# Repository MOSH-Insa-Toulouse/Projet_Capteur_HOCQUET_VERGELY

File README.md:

# Projet Banc de tests 

## Sommaire
<!-- TOC depthFrom:2 -->
  - [1. Description](#1-description)
  - [2. Installation](#2-installation)
  - [3. Code Arduino](#3-code-arduino)
  - [4. Shield KICAD](#4-shield)
  - [5. Application Android](#5-application-android)
  - [6. Etalonnage](#6-Etalonnage)
  - [7. Datasheet](#7-datasheet)
  - [8. Les auteurs](#8-les-auteurs)
<!-- /TOC -->

## 1. Description
Ce répertoire contient toutes les ressources nécessaires au  projet "du capteur au banc de tests" 2021 du Génie Physique de l'INSA de Toulouse. Ce projet est basé sur l'utilisation d'un capteur en graphite, il exploite la dépendance entre la conductivité électrique et l’espace moyen entre les particules au sein d’un système granuleux. L'application de forces entraîne la déformation de l'échantillion, ce qui affecte la distance entre les particules et donc la variataion de la conductivité/resistance globale de l'échantillion.
La chaîne de mesure est basée sur l'acquisition d'un signal associé à la variation de résistance du capteur. Notre shield permet de conditionner, filtrer et amplifier (ampli transimpédance) le signal afin de transmettre une tension exploitable par une carte arduino UNO. Par ailleurs, il fait aussi le lien entre la carte et les différents modules : module bluetooth, encodeur rotateur, écran oled. 
Les mesures sont aussi transmises en bluetooth et interfacées sur une application mobile que nous avons conçue sur MIT App Inventor.

## 2. Installation

### Préparation du shield 
Utilisez le fichier gerber pour imprimer le shield, puis utilisez le schéma et fiche technique pour le choix et le positionnement des composants. Une fois les composants et les pattes soudées, vous pouvez brancher le shield sur l'arduino UNO.

### Codes 
Vous pouvez ensuite récupérer le code arduino depuis le fichier "Code Arduino" de ce répertoire et directement le téléverser sur la carte. Concernant l'application mobile, il vous suffit de récupérer et d'installer le .apk placé dans le fichier "application mobile" du répertoire.
Vous êtes maintenant prêts à réaliser vos premières mesures !

## 3. Code Arduino

Notre code Arduino (C++) que vous retrouverez dans le fichier du même nom, permet : de lire la tension tension de sortie de l'ampli transimpédance sur 10 bits, d'afficher le signal sur un écran OLED 128x64 en Volts ou en Ohm sur 10 bits, de transmettre la tension par bluetooth sur 1 otect à travers le module hc-05 et d'acquerir les rotations d'un encodeur rotatoire afin de changer l'affichage de l'écran OLED.

## 4. Shield

Le shield a été conçu sous KiCad, il contient un amplificateur transimpédance adapté à notre utilisation, ainsi que des socles pour alimenter et communiquer avec les différents modules. Vous pouvez retrouver l'ensemble du projet, et les fichiers nécessaires à l'impression dans le fichier "Shield_KiCad".

## 5. Application Android

Nous avons prototypé une application mobile capable de recevoir la tension associée à la mesure sur 1 octet et de la traiter. Elle dispose de plusieurs options qui permettent de convertir la tension en resistance, de fixer R0 (la résistance sans contrainte appliquée) et d'afficher en temps réel l'évolution relative de la resistance dans un graphique. Il est aussi possible de régler l'échelle du graphique pour mieux visualiser les variations.

## 6. Etalonnage

Un protocole d'étalonnage conçu spécialement pour notre banc de test est présent dans le fichier "Procédure d'étalonnage", il explique en détail la procédure suivie et le matériel que nous conseillons pour obtenir des résultats optimaux. 

## 7. Datasheet

Les conditions d'utilisation, les résultats attendus,  ainsi que les détails sur chaque partie de la chaîne de mesures sont donnés dans la datasheet que vous pouvez retrouver dans le fichier au même nom. 

## 8. Les auteurs

Projet réalisé par des étudiants en 4 ième année du Génie Physique de l'INSA de Toulouse:

**Henri Hocquet et Fabien Vergely**

- Mail : _henrii.hocquet@gmail.com_

- Mail : _fabien.vergely@gmail.com_

Si vous avez des questions n'hésitez pas ;)

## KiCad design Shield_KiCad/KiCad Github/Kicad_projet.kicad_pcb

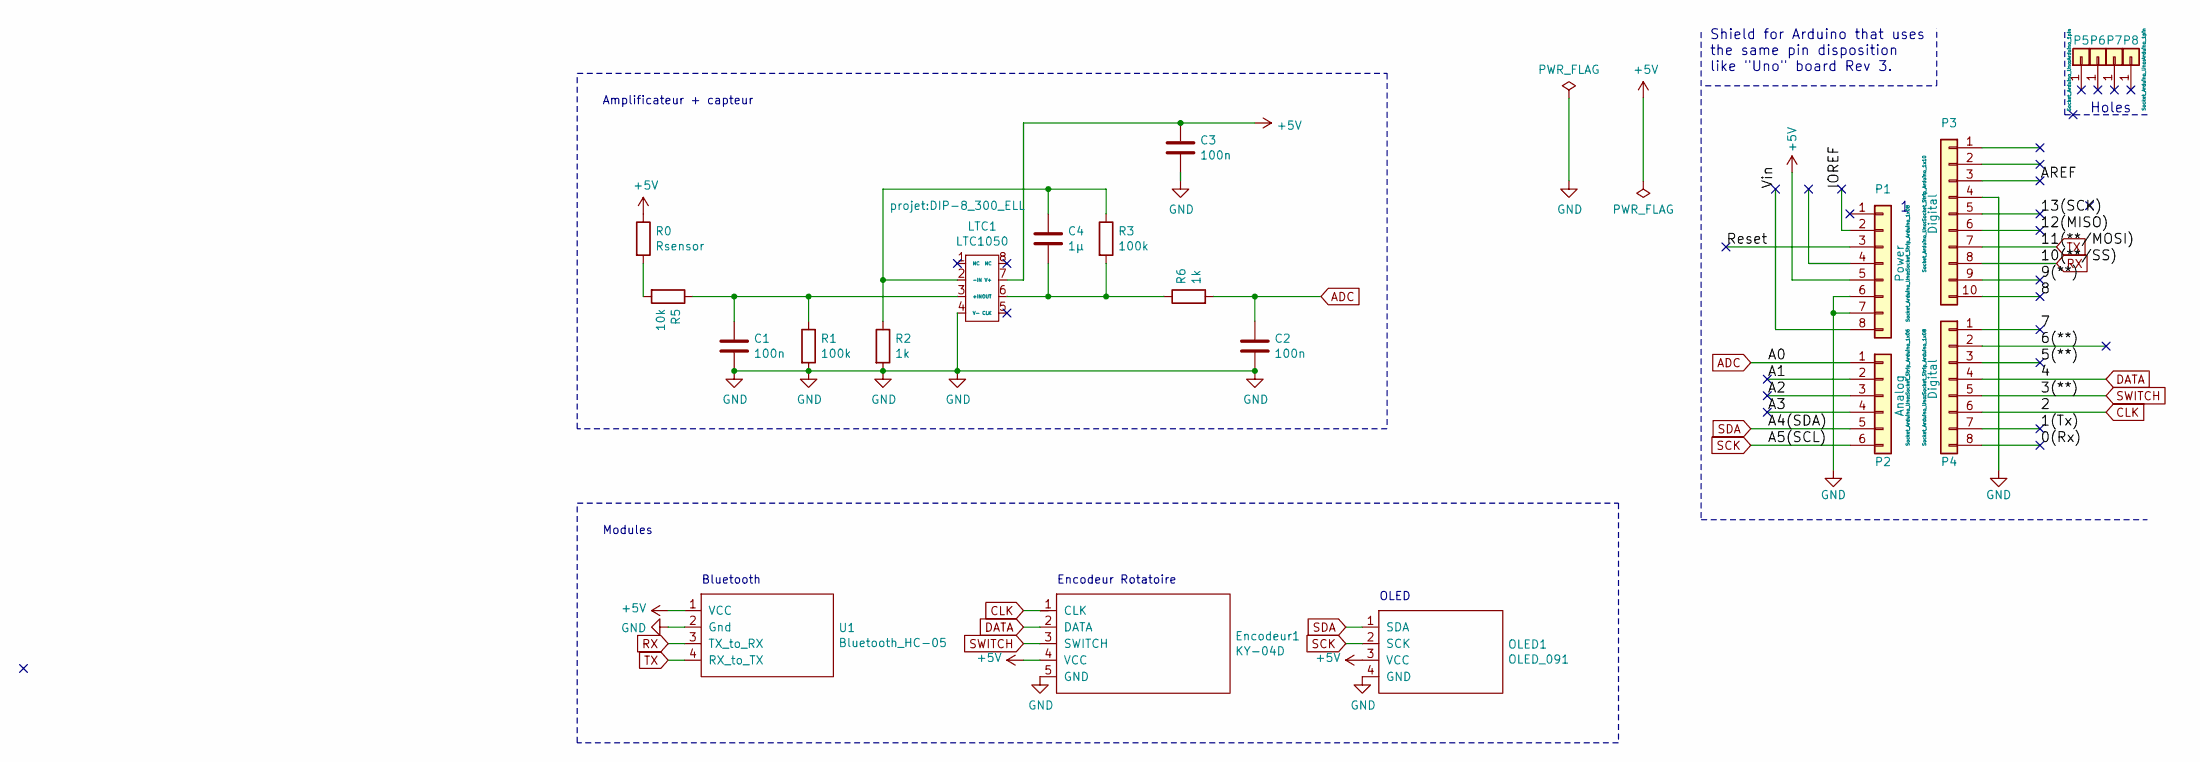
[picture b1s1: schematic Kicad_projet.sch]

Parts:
C1, C2, C3: 100n; C_Disc_D3.0mm_W1.6mm_P2.50mm
C4: 1µ; C_Rect_L7.0mm_W3.5mm_P5.00mm
Encodeur1: KY-04D; Encodeur
LTC1: LTC1050; DIP-8_300_ELL
OLED1: OLED_091; OLED
P1: Power; Socket_Strip_Arduino_1x08
P2: Analog; Socket_Strip_Arduino_1x06
P3: Digital; Socket_Strip_Arduino_1x10
P4: Digital; Socket_Strip_Arduino_1x08
P5, P6, P7, P8: CONN_01X01; Arduino_1pin
R0: Rsensor; R_Axial_DIN0204_L3.6mm_D1.6mm_P2.54mm_Vertical
R1, R3: 100k; R_Axial_DIN0309_L9.0mm_D3.2mm_P12.70mm_Horizontal
R2, R6: 1k; R_Axial_DIN0309_L9.0mm_D3.2mm_P12.70mm_Horizontal
R5: 10k; R_Axial_DIN0309_L9.0mm_D3.2mm_P12.70mm_Horizontal
U1: Bluetooth_HC-05

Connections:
+5V: C3.1, Encodeur1.4 (VCC), LTC1.7 (V+), OLED1.3 (VCC), P1.5, R0.1, U1.1 (VCC)
/0(Rx): P4.8
/1(Tx): P4.7
/5(**): P4.3
/6(**): P4.2
/7: P4.1
/8: P3.10
/9(**): P3.9
/12(MISO): P3.6
/13(SCK): P3.5
/A1: P2.2
/A2: P2.3
/A3: P2.4
/AREF: P3.3
/IOREF: P1.2
/Reset: P1.3
/Vin: P1.8
ADC: C2.1, P2.1, R6.2
CLK: Encodeur1.1 (CLK), P4.6
DATA: Encodeur1.2 (DATA), P4.4
GND: C1.2, C2.2, C3.2, Encodeur1.5 (GND), LTC1.4 (V-), OLED1.4 (GND), P1.6, P1.7, P3.4, R1.2, R2.2, U1.2 (Gnd)
unnamed: C1.1, LTC1.3 (+IN), R1.1, R5.1
unnamed: C4.1, LTC1.2 (-IN), R2.1, R3.1
unnamed: C4.2, LTC1.6 (OUT), R3.2, R6.1
unnamed: R0.2, R5.2
RX: P3.8, U1.3 (TX_to_RX)
SCK: OLED1.2 (SCK), P2.6
SDA: OLED1.1 (SDA), P2.5
SWITCH: Encodeur1.3 (SWITCH), P4.5
TX: P3.7, U1.4 (RX_to_TX)

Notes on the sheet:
Holes
Shield for Arduino that uses the same pin disposition like "Uno" board Rev 3.
Amplificateur + capteur
Modules
Bluetooth
Encodeur Rotatoire
OLED

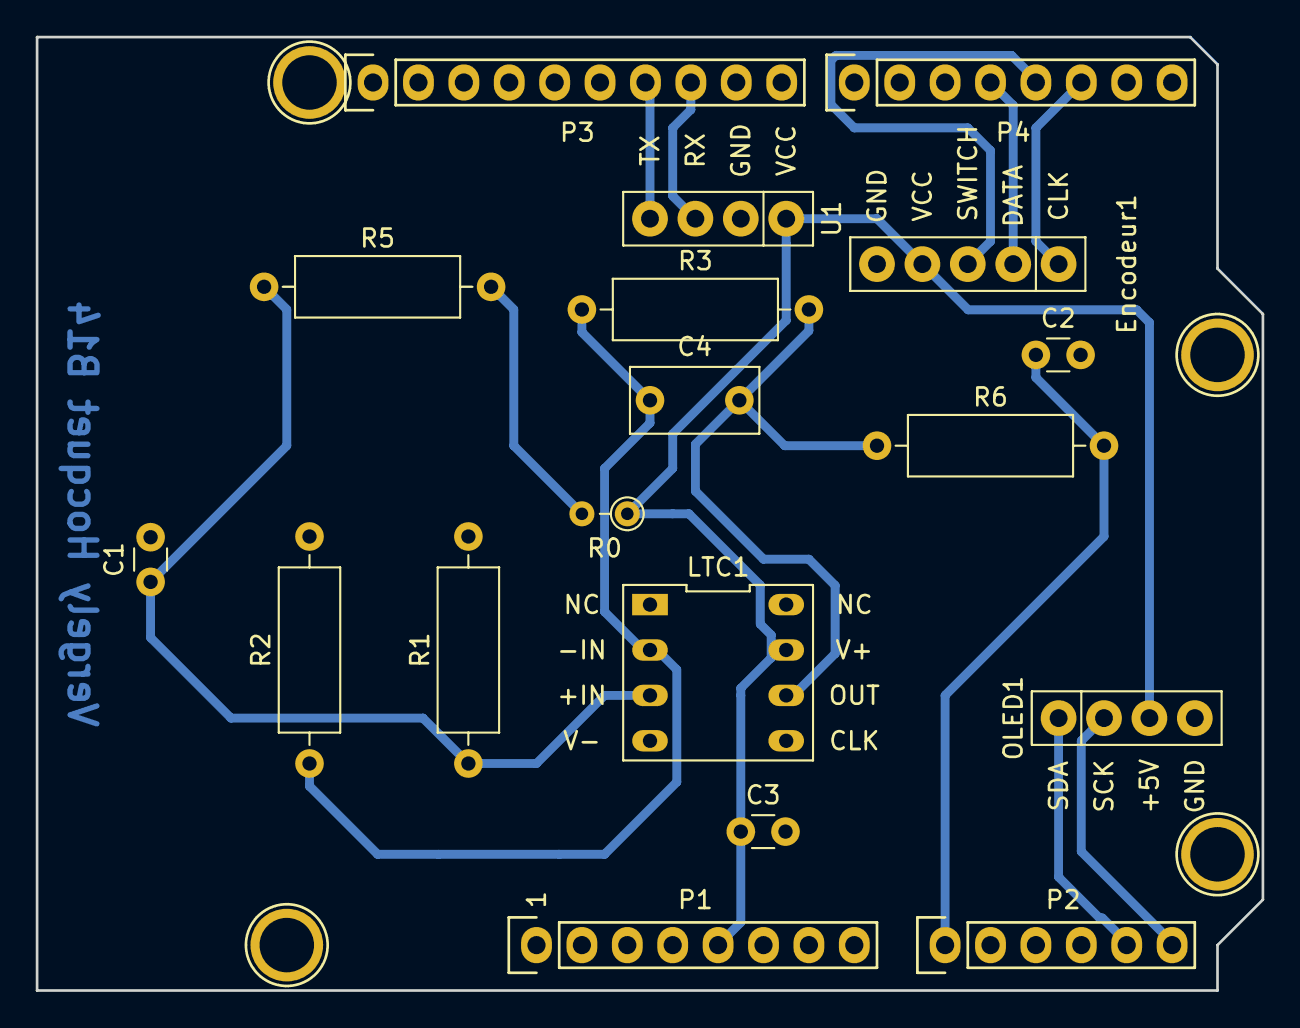
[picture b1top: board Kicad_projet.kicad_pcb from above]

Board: 2 copper layers, 68.6 x 53.3 mm, 22 parts (0 on the bottom side), 14 nets.

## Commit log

2021-03-27 code C
2021-03-27 appli
2021-03-27 Librairies
2021-03-27 Mesures
2021-03-27 Procedures
2021-03-27 shield
2021-05-01 Add files via upload
    Datasheet
